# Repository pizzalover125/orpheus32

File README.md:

# orpheus32

An ESP32 devboard made for Hack Club. A rival to the famous Orpheus Pico. 

### features
- 23 GPIO
- Integrated WiFi + Bluetooth
- 2x UART
- 2x DAC (8-bit)
- SPI, I2C, I2S support
- User-addressable NeoPixel

### schematic + PCB

### KiCAD Render

### BOM
- PCB: $40.30 (incl. JLCPCB PCB, Assembly, Shipping, Customs, Taxes)
- Detailed BOM located in BOM.csv

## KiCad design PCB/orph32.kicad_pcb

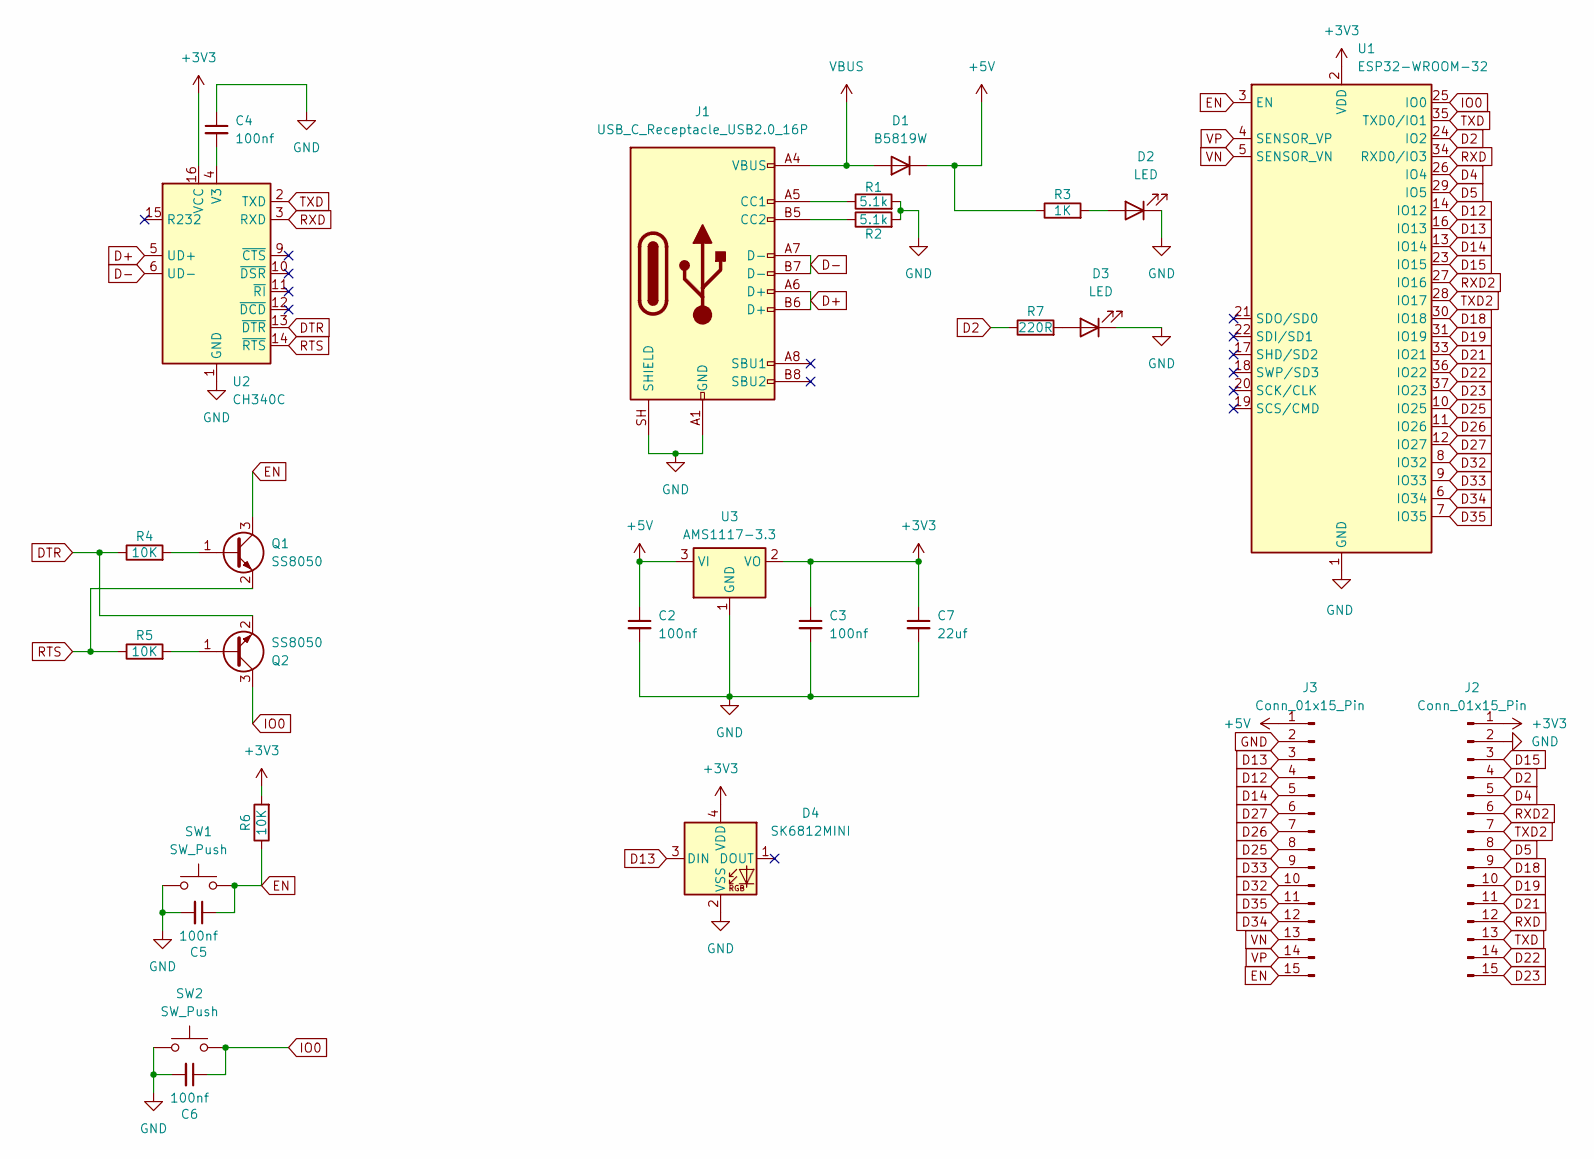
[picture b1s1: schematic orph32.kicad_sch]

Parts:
C2, C3, C4, C5, C6: 100nf; C_0603_1608Metric
C7: 22uf; C_0603_1608Metric
D1: B5819W; D_SOD-123
D2, D3: LED; LED_0603_1608Metric
D4: SK6812MINI; LED_SK6812MINI_PLCC4_3.5x3.5mm_P1.75mm
J1: USB_C_Receptacle_USB2.0_16P; USB_C_Receptacle_HRO_TYPE-C-31-M-12
J2, J3: Conn_01x15_Pin; PinHeader_1x15_P2.54mm_Vertical
Q1, Q2: SS8050; SOT-23
R1, R2: 5.1k; R_0603_1608Metric
R3: 1K; R_0603_1608Metric
R4, R5, R6: 10K; R_0603_1608Metric
R7: 220R; R_0603_1608Metric
SW1, SW2: SW_Push; SW_Push_SPST_NO_Alps_SKRK
U1: ESP32-WROOM-32
U2: CH340C; SOIC-16_3.9x9.9mm_P1.27mm
U3: AMS1117-3.3; SOT-223-3_TabPin2

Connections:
+3V3: C3.1, C7.1, D4.4 (VDD), J2.1, R6.2, U1.2 (VDD), U2.16 (VCC), U3.2 (VO)
+5V: C2.1, D1.1 (K), J3.1, R3.1, U3.3 (VI)
D2: J2.4, R7.1, U1.24 (IO2)
D4: J2.5, U1.26 (IO4)
D5: J2.8, U1.29 (IO5)
D12: J3.4, U1.14 (IO12)
D13: D4.3 (DIN), J3.3, U1.16 (IO13)
D14: J3.5, U1.13 (IO14)
D15: J2.3, U1.23 (IO15)
D18: J2.9, U1.30 (IO18)
D19: J2.10, U1.31 (IO19)
D21: J2.11, U1.33 (IO21)
D22: J2.14, U1.36 (IO22)
D23: J2.15, U1.37 (IO23)
D25: J3.8, U1.10 (IO25)
D26: J3.7, U1.11 (IO26)
D27: J3.6, U1.12 (IO27)
D32: J3.10, U1.8 (IO32)
D33: J3.9, U1.9 (IO33)
D34: J3.12, U1.6 (IO34)
D35: J3.11, U1.7 (IO35)
D+: J1.A6 (D+), J1.B6 (D+), U2.5 (UD+)
D-: J1.A7 (D-), J1.B7 (D-), U2.6 (UD-)
DTR: Q2.2 (E), R4.1, U2.13 (~DTR)
EN: C5.1, J3.15, Q1.3 (C), R6.1, SW1.2, U1.3 (EN)
GND: C2.2, C3.2, C4.1, C5.2, C6.2, C7.2, D2.1 (K), D3.1 (K), D4.2 (VSS), J1.A1 (GND), J1.A12 (GND), J1.B1 (GND), J1.B12 (GND), J1.SH (SHIELD), J2.2, J3.2, R1.2, R2.2, SW1.1, SW2.1, U1.1 (GND), U1.15 (GND), U1.38 (GND), U1.39 (GND), U2.1 (GND), U3.1 (GND)
IO0: C6.1, Q2.3 (C), SW2.2, U1.25 (IO0)
unnamed: D2.2 (A), R3.2
unnamed: D3.2 (A), R7.2
unnamed: J1.A5 (CC1), R1.1
unnamed: J1.B5 (CC2), R2.1
unnamed: Q1.1 (B), R4.2
unnamed: Q2.1 (B), R5.2
unnamed: C4.2, U2.4 (V3)
RTS: Q1.2 (E), R5.1, U2.14 (~RTS)
RXD: J2.12, U1.34 (RXD0/IO3), U2.3 (RXD)
RXD2: J2.6, U1.27 (IO16)
TXD: J2.13, U1.35 (TXD0/IO1), U2.2 (TXD)
TXD2: J2.7, U1.28 (IO17)
VBUS: D1.2 (A), J1.A4 (VBUS), J1.A9 (VBUS), J1.B4 (VBUS), J1.B9 (VBUS)
VN: J3.13, U1.5 (SENSOR_VN)
VP: J3.14, U1.4 (SENSOR_VP)

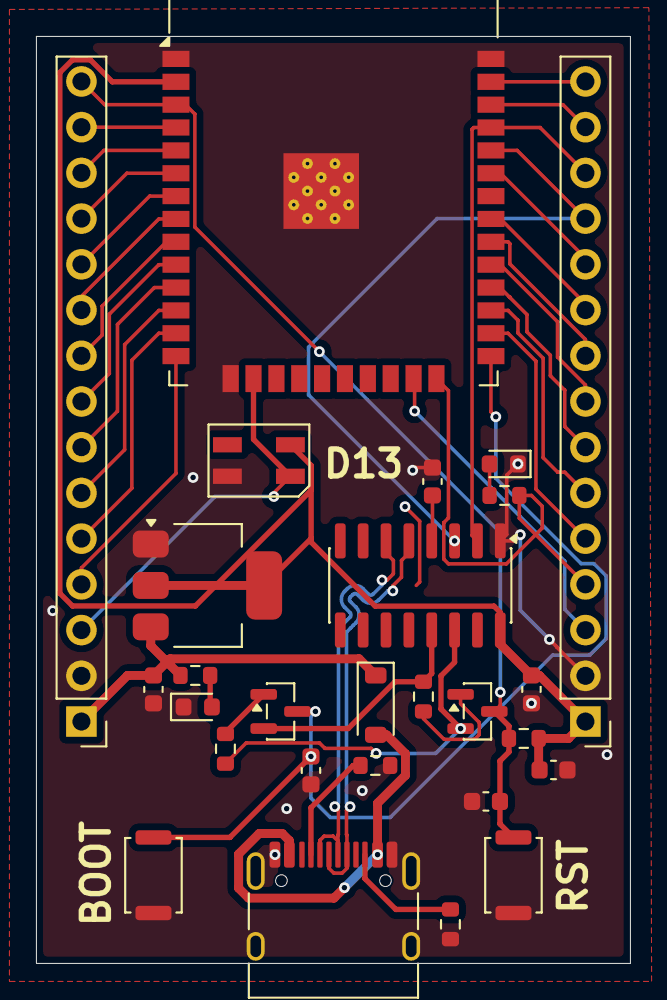
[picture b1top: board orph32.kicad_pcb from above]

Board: 2 copper layers, 33.0 x 51.5 mm, 27 parts (0 on the bottom side), 42 nets.

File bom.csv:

Designator,Footprint,Quantity,Value,LCSC Part #
"C2, C3, C4, C5, C6",0603,5,100nf,
C7,0603,1,22uf,
D1,D_SOD-123,1,B5819W,
"D2, D3",0603,2,LED,
D4,LED_SK6812MINI_PLCC4_3.5x3.5mm_P1.75mm,1,SK6812MINI,
J1,USB_C_Receptacle_HRO_TYPE-C-31-M-12,1,USB_C_Receptacle_USB2.0_16P,
"J2, J3",PinHeader_1x15_P2.54mm_Vertical,2,Conn_01x15_Pin,
"Q1, Q2",SOT-23,2,SS8050,
"R1, R2",0603,2,5.1k,
R3,0603,1,1K,
"R4, R5, R6",0603,3,10K,
R7,0603,1,220R,
"SW1, SW2",SW_Push_SPST_NO_Alps_SKRK,2,SW_Push,
U1,ESP32-WROOM-32,1,ESP32-WROOM-32,
U2,SOIC-16_3.9x9.9mm_P1.27mm,1,CH340C,
U3,SOT-223-3_TabPin2,1,AMS1117-3.3,

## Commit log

2026-05-20 Revise JOURNAL.md with updates on rev 3
    Updated the time spent on rev 3 and added additional notes on sensor board development.
2026-05-20 Update journal entry for rev 3.1 to rev 3
2026-05-21 Revise JOURNAL.md with new PCB design updates
    Updated revision details and added new entries for PCB design progress.
2026-05-22 added everything
